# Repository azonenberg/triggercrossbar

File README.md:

# PROJECT STATUS

You probably don't want to build this as is, there's a couple of bugs. May or may not respin later on with fixes, for now I'm just bodging my prototype.

Bodge log at https://docs.google.com/document/d/14ighvhOLtBR-3ShkNhyRGlamA1f7WH5_sXfJCJYxb1o/edit

# What is it?

When finished, it will be a 1U rack-mountable appliance with a TBD number of BNC and/or SMA connectors on the back side for trigger inputs and outputs. Some will be input only, some output only, and some bidirectional. Exact mix is TBD.

Additionally, a front panel SMA input will be connected through a precision 10 GHz comparator (ADI HMC675LP3E) to an FPGA transceiver input, allowing single ended CDR triggering.

There may or may not be front panel SMA inputs/outputs connected to otherwise unused transceiver channels for expansion or additional trigger capabilities.

An Ethernet SCPI interface will allow configuration of an FPGA-based crossbar, with the internal CDR trigger as well as all of the input channels available as inputs. Any input can be forwarded to any output, allowing arbitrary cross-triggering of attached instruments without the need to recable.

Front panel LEDs with pulse stretching will display the states of trigger in/out ports.

This system is intended in part as a testbed to de-risk several future projects (validating stackup and power supply design etc), and to use up an FPGA that I had lying around the lab. Only one unit is ever expected to be built, so a functionally equivalent platform could definitely be built for lower cost.

# Physical architecture

# Trigger ports

Koaxis AL62-CC086F-RL10-6.00-MK (6" CC086F hand formable FEP jacket SMA - SMPM), length open to change based on final mechanical and board design.

## Input range

The range of the inputs should be sufficient to accommodate all common T&M instruments, which will likely require variable thresholding.

Representative instrument trigger output specs:

* PicoScope 6000E (bidirectional): not specified, need to measure
* PicoVNA 108: 3.3V into high-Z
* Siglent SSG5000X (bidirectional): 5V TTL for trigger, 3.3V CMOS for pulse
* Siglent SDG7000A: 5V TTL (voh = 3.8V)
* Teledyne LeCroy (all recent models): 1V into 1M ohm / 500 mV into 50 ohm by default, adjustable a bit?

## Output range

The range of the outputs should be compatible with all common T&M instruments, which will likely require variable swing.

Representative instrument trigger input specs:

* PicoScope 6000E (bidirectional): 2.5V CMOS high-z input, fixed 1.25V threshold
* PicoVNA 108: 3.3V CMOS high-Z, nominal 1.5V threshold
* Siglent SSG5000X (bidirectional): 5V TTL for trigger, 3.3V CMOS for pulse
* Siglent SDG7000A: 5V TTL (Vih = 2 to 5.5V)
* Teledyne LeCroy (all recent models): adjustable threshold up to +/- 400 mV or +/- 4V in 1x / 10x mode respectively

# Input buffer design

We need a total of seven inputs today, plan for at least ten to provide some margin

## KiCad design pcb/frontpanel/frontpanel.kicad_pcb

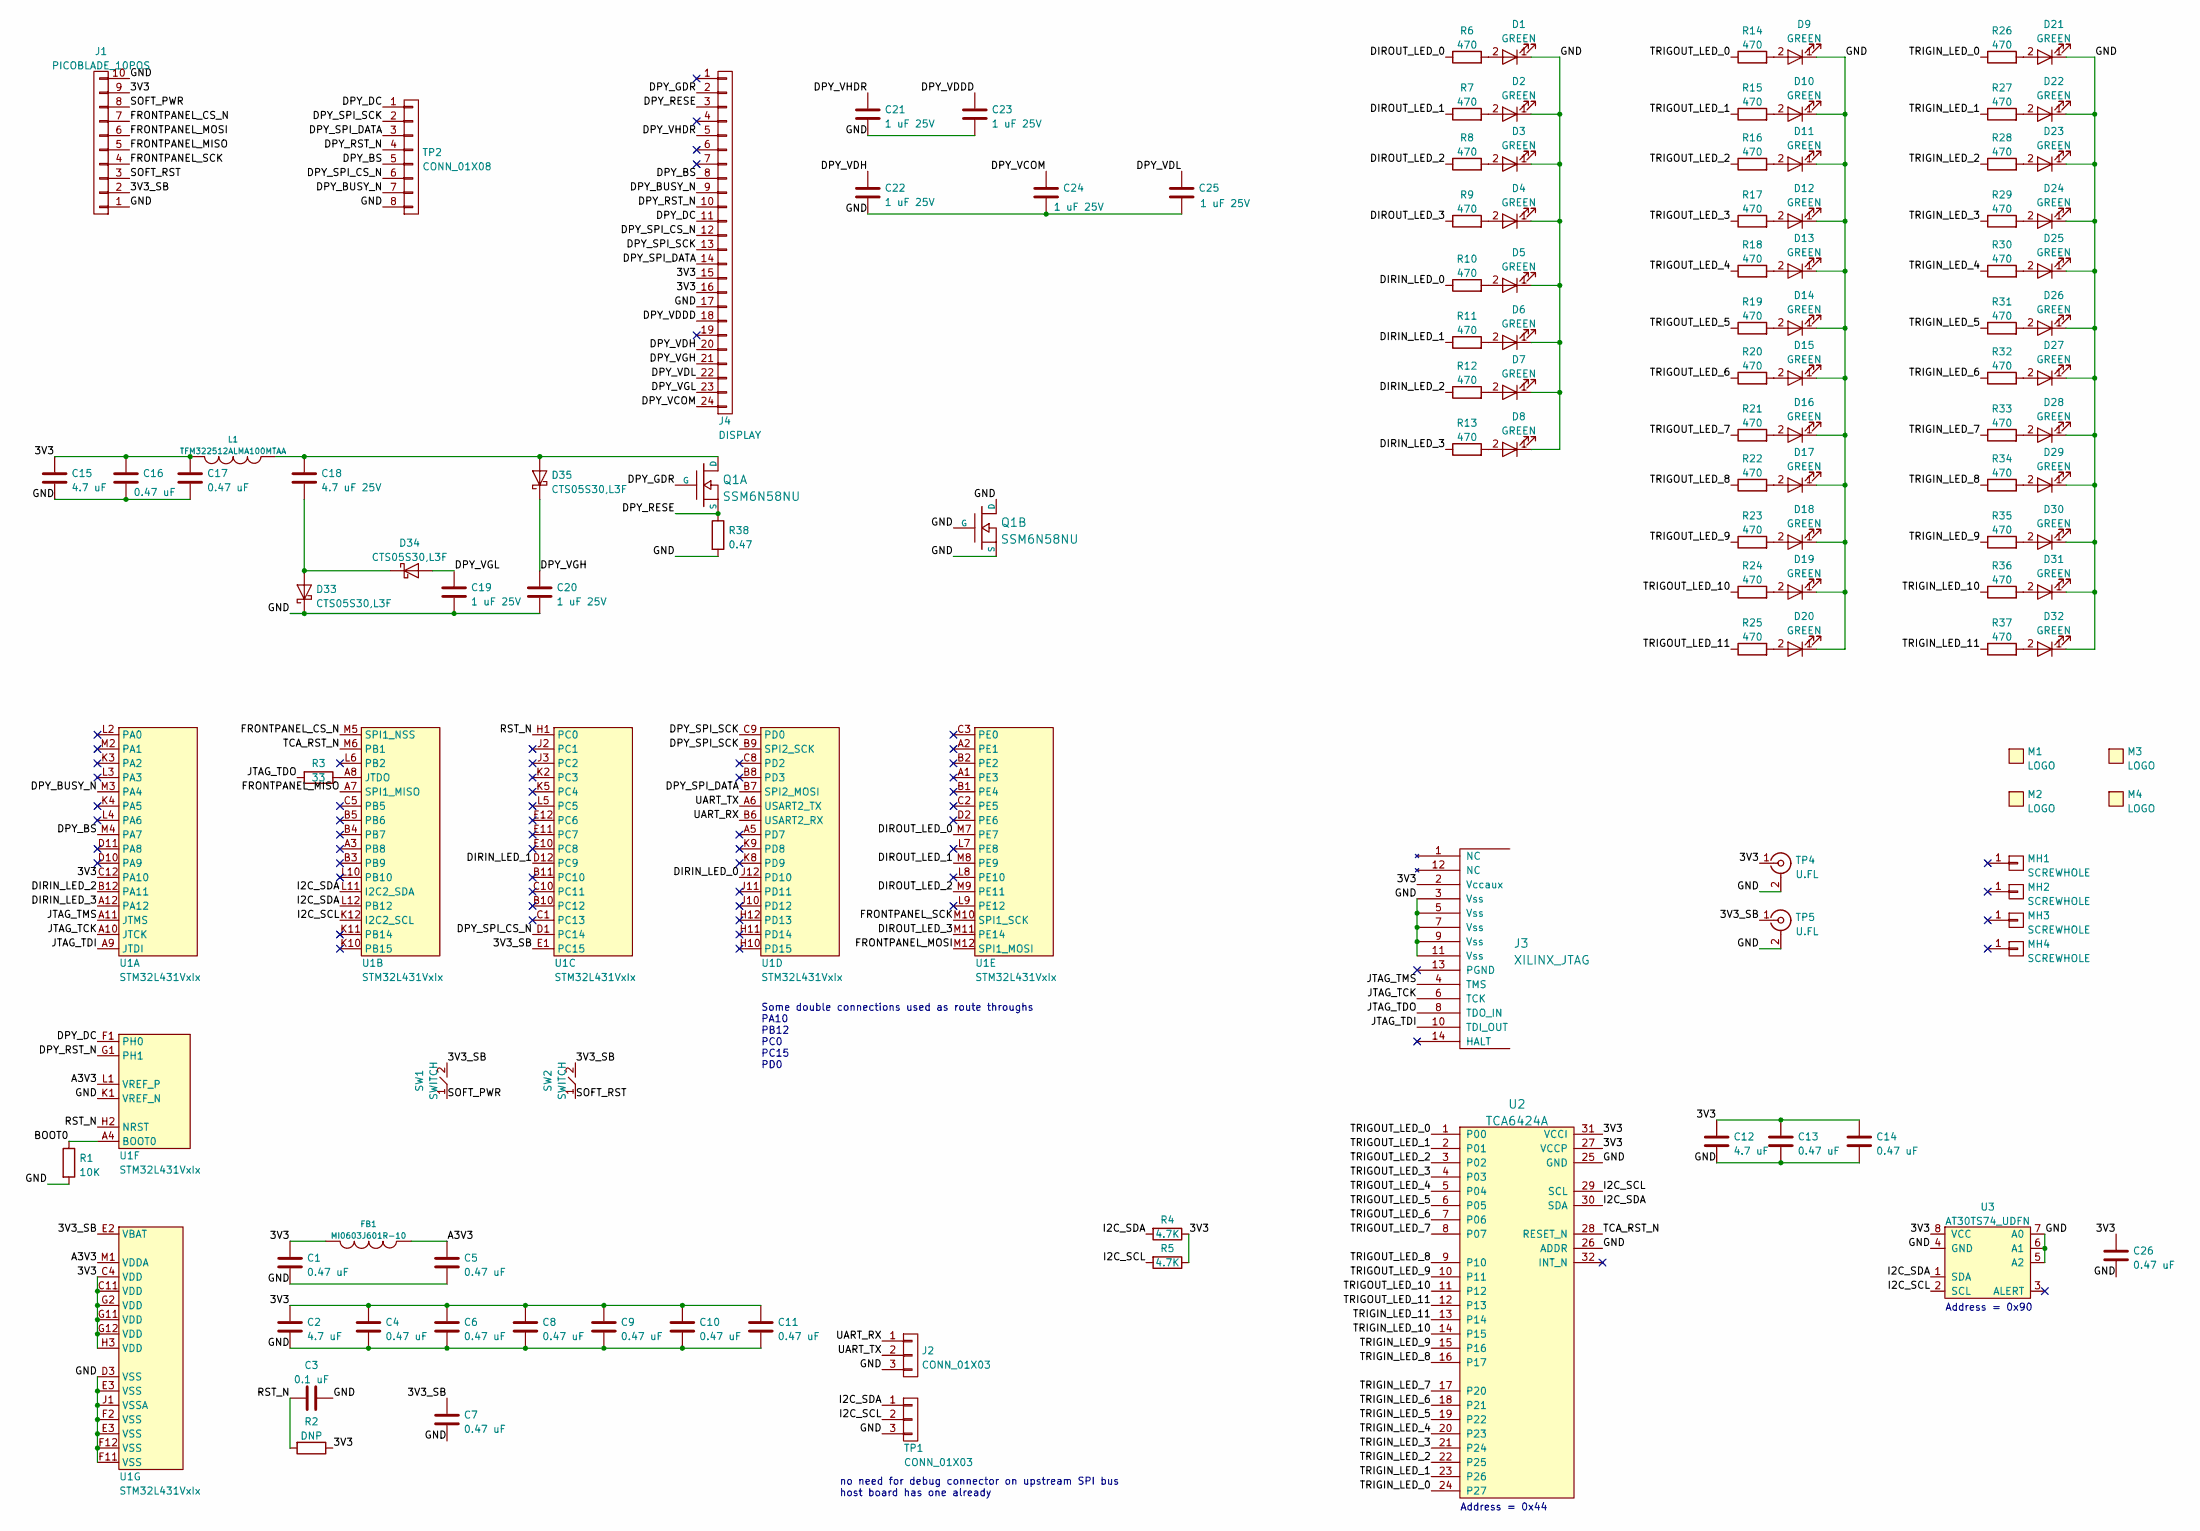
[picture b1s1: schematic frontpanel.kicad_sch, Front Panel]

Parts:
C1, C4, C5, C6, C7, C8, C9, C10, C11, C13, C14, C16, C17, C26: 0.47 uF; EIA_0402_CAP_NOSILK
C2, C12, C15: 4.7 uF; EIA_0603_CAP_NOSILK
C3: 0.1 uF; EIA_0402_CAP_NOSILK
C18: 4.7 uF 25V; EIA_0805_CAP_NOSILK
C19, C20, C21, C22, C23, C24, C25: 1 uF 25V; EIA_0805_CAP_NOSILK
D1, D2, D3, D4, D5, D6, D7, D8, D9, D10, D11, D12, D13, D14, D15, D16, D17, D18, D19, D20, D21, D22, D23, D24, D25, D26, D27, D28, D29, D30, D31, D32: GREEN; EIA_0603_LED
D33, D34, D35: CTS05S30,L3F; SOD882
FB1: MI0603J601R-10; EIA_0603_INDUCTOR_NOSILK
J1: PICOBLADE_10POS; CONN_MOLEX_PICOBLADE_10POS_0532611071
J2: CONN_01X03; CONN_HEADER_2.54MM_1x3
J3: XILINX_JTAG; XILINX_JTAG_PTH_MOLEX_0878311420
J4: DISPLAY; CONN_FFC_0.5MM_1x24_HIROSE_FH34SRJ-24S-0.5SH(50)
L1: TFM322512ALMA100MTAA; EIA_1210_CAP_NOSILK
M1: LOGO; LONGTHING-1200DPI
M2: LOGO; Logo_silk_WEEE_3.4x5mm
M3: LOGO; Logo_silk_OSHW_6x6mm
M4: LOGO; Logo_silk_ROHS_10x5.6mm
MH1, MH2, MH3, MH4: SCREWHOLE; MECHANICAL_CLEARANCEHOLE_4_40
Q1: SSM6N58NU; DFN_6_0.65MM_2x2MM_GDS
R1: 10K; EIA_0402_RES_NOSILK
R2: DNP; EIA_0402_RES_NOSILK
R3: 33; EIA_0402_RES_NOSILK
R4, R5: 4.7K; EIA_0402_RES_NOSILK
R6, R7, R8, R9, R10, R11, R12, R13, R14, R15, R16, R17, R18, R19, R20, R21, R22, R23, R24, R25, R26, R27, R28, R29, R30, R31, R32, R33, R34, R35, R36, R37: 470; EIA_0402_RES_NOSILK
R38: 0.47; EIA_0402_RES_NOSILK
SW1, SW2: SWITCH; SWITCH_RAFI_MICON_5
TP1: CONN_01X03; CONN_HEADER_2.54MM_1x3
TP2: CONN_01X08; CONN_HEADER_2.54MM_1x8
TP4, TP5: U.FL; CONN_U.FL_TE_1909763-1
U1: STM32L431VxIx; BGA_100_7x7_DEPOP_0.5MM_STM32_UFBGA100_OSHPARK
U2: TCA6424A; QFN_32_0.5MM_5x5MM
U3: AT30TS74_UDFN; DFN_8_0.5MM_2x3MM_TALL

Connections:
/3V3: C1.1, C2.1, C4.1, C6.1, C8.1, C9.1, C10.1, C11.1, C12.1, C13.1, C14.1, C15.1, C16.1, C17.1, C26.1, FB1.2, J1.9, J3.2 (Vccaux), J4.15, J4.16, L1.2, R2.1, R4.1, R5.1, TP4.1 (In), U1.C4 (VDD), U1.C11 (VDD), U1.C12 (PA10), U1.G2 (VDD), U1.G11 (VDD), U1.G12 (VDD), U1.H3 (VDD), U2.27 (VCCP), U2.31 (VCCI), U3.8 (VCC)
/3V3_SB: C7.1, J1.2, SW1.2, SW2.2, TP5.1 (In), U1.E1 (PC15), U1.E2 (VBAT)
/A3V3: C5.1, FB1.1, U1.L1 (VREF_P), U1.M1 (VDDA)
/BOOT0: R1.1, U1.A4 (BOOT0)
/DIRIN_LED_0: R10.1, U1.J12 (PD10)
/DIRIN_LED_1: R11.1, U1.D12 (PC9)
/DIRIN_LED_2: R12.1, U1.B12 (PA11)
/DIRIN_LED_3: R13.1, U1.A12
/DIROUT_LED_0: R6.1, U1.M7 (PE7)
/DIROUT_LED_1: R7.1, U1.M8 (PE9)
/DIROUT_LED_2: R8.1, U1.M9 (PE11)
/DIROUT_LED_3: R9.1, U1.M11 (PE14)
/DPY_BS: J4.8, TP2.5, U1.M4 (PA7)
/DPY_BUSY_N: J4.9, TP2.7, U1.M3 (PA4)
/DPY_DC: J4.11, TP2.1, U1.F1 (PH0)
/DPY_GDR: J4.2, Q1.G1 (G)
/DPY_RESE: J4.3, Q1.S1 (S), R38.1
/DPY_RST_N: J4.10, TP2.4, U1.G1 (PH1)
/DPY_SPI_CS_N: J4.12, TP2.6, U1.D1 (PC14)
/DPY_SPI_DATA: J4.14, TP2.3, U1.B7 (SPI2_MOSI)
/DPY_SPI_SCK: J4.13, TP2.2, U1.B9 (SPI2_SCK), U1.C9 (PD0)
/DPY_VCOM: C24.1, J4.24
/DPY_VDDD: C23.1, J4.18
/DPY_VDH: C22.1, J4.20
/DPY_VDL: C25.1, J4.22
/DPY_VGH: C20.1, D35.1 (K), J4.21
/DPY_VGL: C19.1, D34.2 (A), J4.23
/DPY_VHDR: C21.1, J4.5
/FRONTPANEL_CS_N: J1.7, U1.M5 (SPI1_NSS)
/FRONTPANEL_MISO: J1.5, U1.A7 (SPI1_MISO)
/FRONTPANEL_MOSI: J1.6, U1.M12 (SPI1_MOSI)
/FRONTPANEL_SCK: J1.4, U1.M10 (SPI1_SCK)
/GND: C1.2, C2.2, C3.2, C4.2, C5.2, C6.2, C7.2, C8.2, C9.2, C10.2, C11.2, C12.2, C13.2, C14.2, C15.2, C16.2, C17.2, C19.2, C20.2, C21.2, C22.2, C23.2, C24.2, C25.2, C26.2, D1.1 (K), D2.1 (K), D3.1 (K), D4.1 (K), D5.1 (K), D6.1 (K), D7.1 (K), D8.1 (K), D9.1 (K), D10.1 (K), D11.1 (K), D12.1 (K), D13.1 (K), D14.1 (K), D15.1 (K), D16.1 (K), D17.1 (K), D18.1 (K), D19.1 (K), D20.1 (K), D21.1 (K), D22.1 (K), D23.1 (K), D24.1 (K), D25.1 (K), D26.1 (K), D27.1 (K), D28.1 (K), D29.1 (K), D30.1 (K), D31.1 (K), D32.1 (K), D33.1 (K), J1.1, J1.10, J2.3, J3.3 (Vss), J3.5 (Vss), J3.7 (Vss), J3.9 (Vss), J3.11 (Vss), J4.17, Q1.D2 (D), Q1.G2 (G), Q1.S2 (S), R1.2, R38.2, TP1.3, TP2.8, TP4.2 (Ext), TP5.2 (Ext), U1.D3 (VSS), U1.E3 (VSS), U1.F2 (VSS), U1.F11 (VSS), U1.F12 (VSS), U1.J1 (VSSA), U1.K1 (VREF_N), U2.25 (GND), U2.26 (ADDR), U3.4 (GND), U3.5 (A2), U3.6 (A1), U3.7 (A0)
/I2C_SCL: R5.2, TP1.2, U1.K12 (I2C2_SCL), U2.29 (SCL), U3.2 (SCL)
/I2C_SDA: R4.2, TP1.1, U1.L11 (I2C2_SDA), U1.L12 (PB12), U2.30 (SDA), U3.1 (SDA)
/JTAG_TCK: J3.6 (TCK), U1.A10 (JTCK)
/JTAG_TDI: J3.10 (TDI_OUT), U1.A9 (JTDI)
/JTAG_TDO: J3.8 (TDO_IN), R3.2
/JTAG_TMS: J3.4 (TMS), U1.A11 (JTMS)
/RST_N: C3.1, R2.2, U1.H1 (PC0), U1.H2 (NRST)
/SOFT_PWR: J1.8, SW1.1
/SOFT_RST: J1.3, SW2.1
/TCA_RST_N: U1.M6 (PB1), U2.28 (RESET_N)
/TRIGIN_LED_0: R26.1, U2.24 (P27)
/TRIGIN_LED_1: R27.1, U2.23 (P26)
/TRIGIN_LED_2: R28.1, U2.22 (P25)
/TRIGIN_LED_3: R29.1, U2.21 (P24)
/TRIGIN_LED_4: R30.1, U2.20 (P23)
/TRIGIN_LED_5: R31.1, U2.19 (P22)
/TRIGIN_LED_6: R32.1, U2.18 (P21)
/TRIGIN_LED_7: R33.1, U2.17 (P20)
/TRIGIN_LED_8: R34.1, U2.16 (P17)
/TRIGIN_LED_9: R35.1, U2.15 (P16)
/TRIGIN_LED_10: R36.1, U2.14 (P15)
/TRIGIN_LED_11: R37.1, U2.13 (P14)
/TRIGOUT_LED_0: R14.1, U2.1 (P00)
/TRIGOUT_LED_1: R15.1, U2.2 (P01)
/TRIGOUT_LED_2: R16.1, U2.3 (P02)
/TRIGOUT_LED_3: R17.1, U2.4 (P03)
/TRIGOUT_LED_4: R18.1, U2.5 (P04)
/TRIGOUT_LED_5: R19.1, U2.6 (P05)
/TRIGOUT_LED_6: R20.1, U2.7 (P06)
/TRIGOUT_LED_7: R21.1, U2.8 (P07)
/TRIGOUT_LED_8: R22.1, U2.9 (P10)
/TRIGOUT_LED_9: R23.1, U2.10 (P11)
/TRIGOUT_LED_10: R24.1, U2.11 (P12)
/TRIGOUT_LED_11: R25.1, U2.12 (P13)
/UART_RX: J2.1, U1.B6 (USART2_RX)
/UART_TX: J2.2, U1.A6 (USART2_TX)
unnamed: C18.1, D35.2 (A), L1.1, Q1.D1 (D)
unnamed: C18.2, D33.2 (A), D34.1 (K)
unnamed: D1.2 (A), R6.2
unnamed: D2.2 (A), R7.2
unnamed: D3.2 (A), R8.2
unnamed: D4.2 (A), R9.2
unnamed: D5.2 (A), R10.2
unnamed: D6.2 (A), R11.2
unnamed: D7.2 (A), R12.2
unnamed: D8.2 (A), R13.2
unnamed: D9.2 (A), R14.2
unnamed: D10.2 (A), R15.2
unnamed: D11.2 (A), R16.2
unnamed: D12.2 (A), R17.2
unnamed: D13.2 (A), R18.2
unnamed: D14.2 (A), R19.2
unnamed: D15.2 (A), R20.2
unnamed: D16.2 (A), R21.2
unnamed: D17.2 (A), R22.2
unnamed: D18.2 (A), R23.2
unnamed: D19.2 (A), R24.2
unnamed: D20.2 (A), R25.2
unnamed: D21.2 (A), R26.2
unnamed: D22.2 (A), R27.2
unnamed: D23.2 (A), R28.2
unnamed: D24.2 (A), R29.2
unnamed: D25.2 (A), R30.2
unnamed: D26.2 (A), R31.2
unnamed: D27.2 (A), R32.2
unnamed: D28.2 (A), R33.2
unnamed: D29.2 (A), R34.2
unnamed: D30.2 (A), R35.2
unnamed: D31.2 (A), R36.2
unnamed: D32.2 (A), R37.2
unnamed: R3.1, U1.A8 (JTDO)

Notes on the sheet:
Address = 0x90
no need for debug connector on upstream SPI bus host board has one already
Address = 0x44
Some double connections used as route throughs PA10 PB12 PC0 PC15 PD0

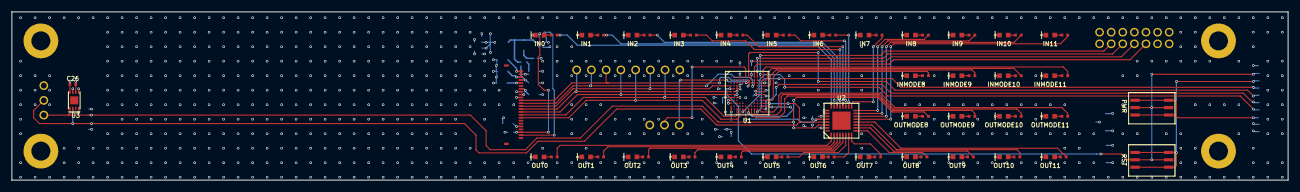
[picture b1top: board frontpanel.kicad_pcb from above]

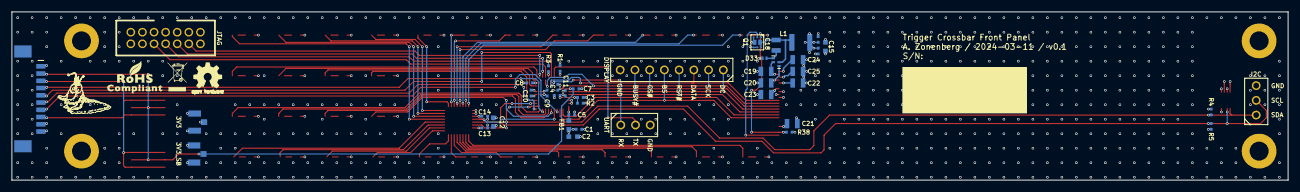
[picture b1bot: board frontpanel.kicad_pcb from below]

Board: 4 copper layers, 220.0 x 29.0 mm, 123 parts (52 on the bottom side), 104 nets.

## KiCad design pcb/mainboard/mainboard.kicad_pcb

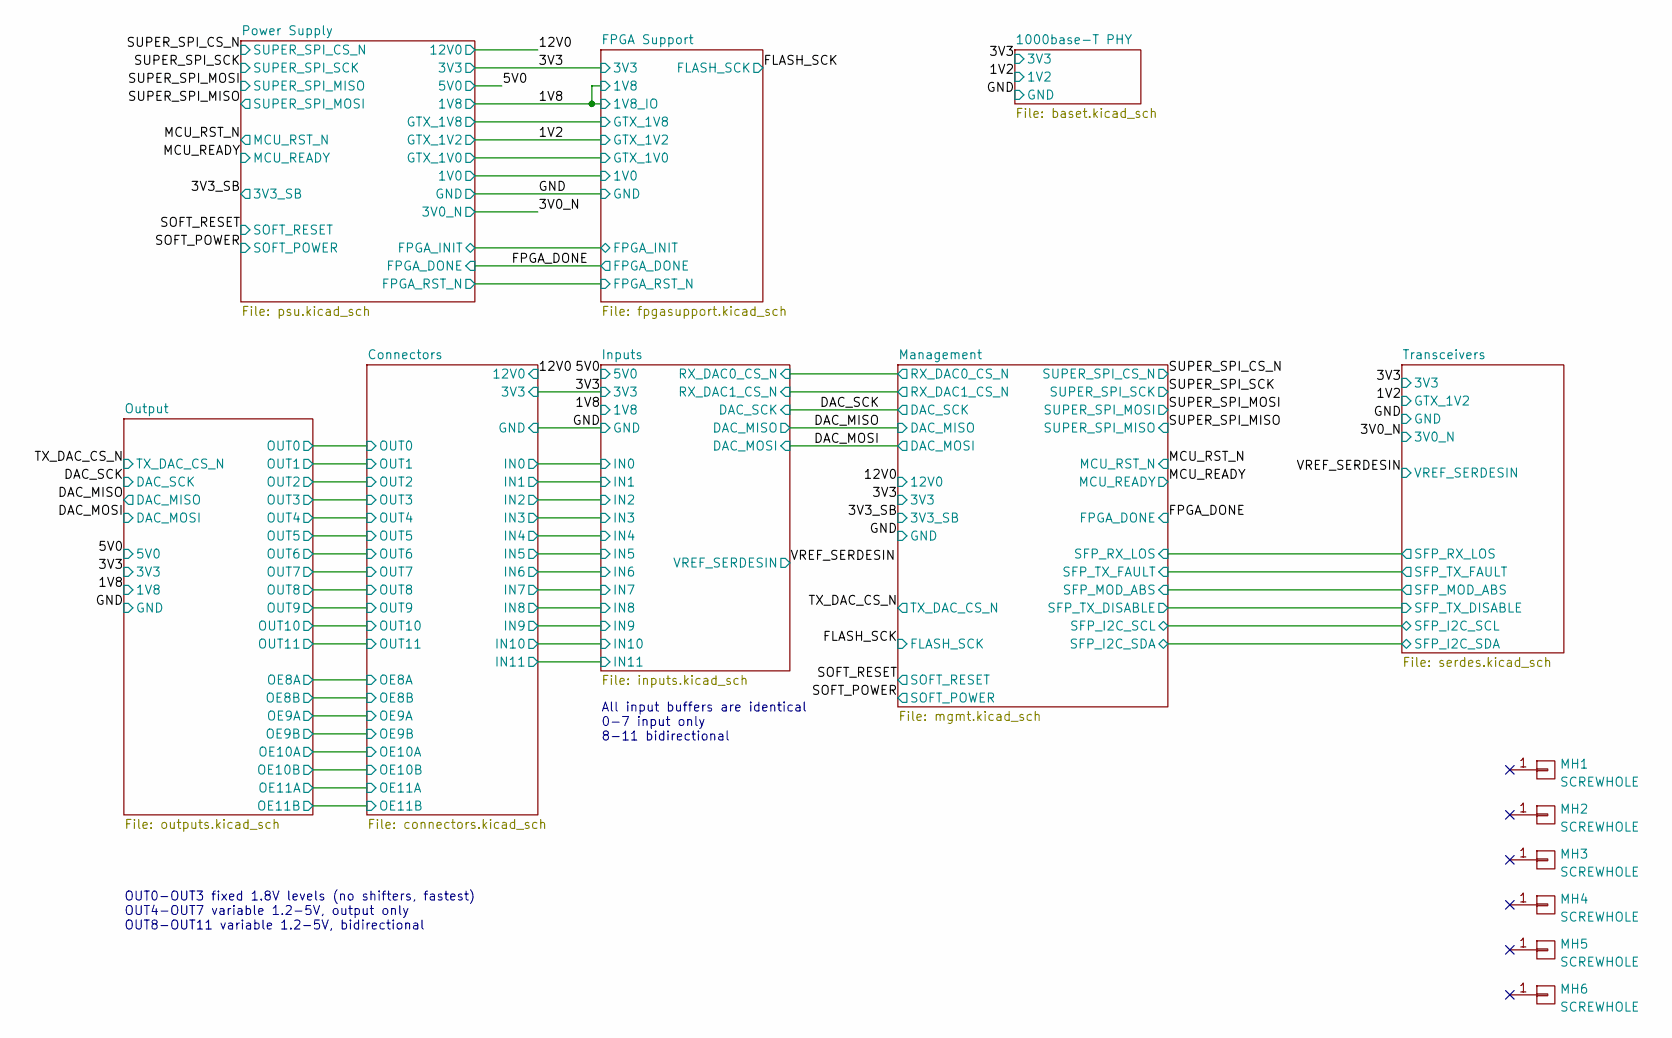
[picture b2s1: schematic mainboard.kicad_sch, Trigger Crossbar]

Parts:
MH1, MH2, MH3, MH4, MH5, MH6: SCREWHOLE; MECHANICAL_CLEARANCEHOLE_4_40

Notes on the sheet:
All input buffers are identical 0-7 input only 8-11 bidirectional
OUT0-OUT3 fixed 1.8V levels (no shifters, fastest) OUT4-OUT7 variable 1.2-5V, output only OUT8-OUT11 variable 1.2-5V, bidirectional

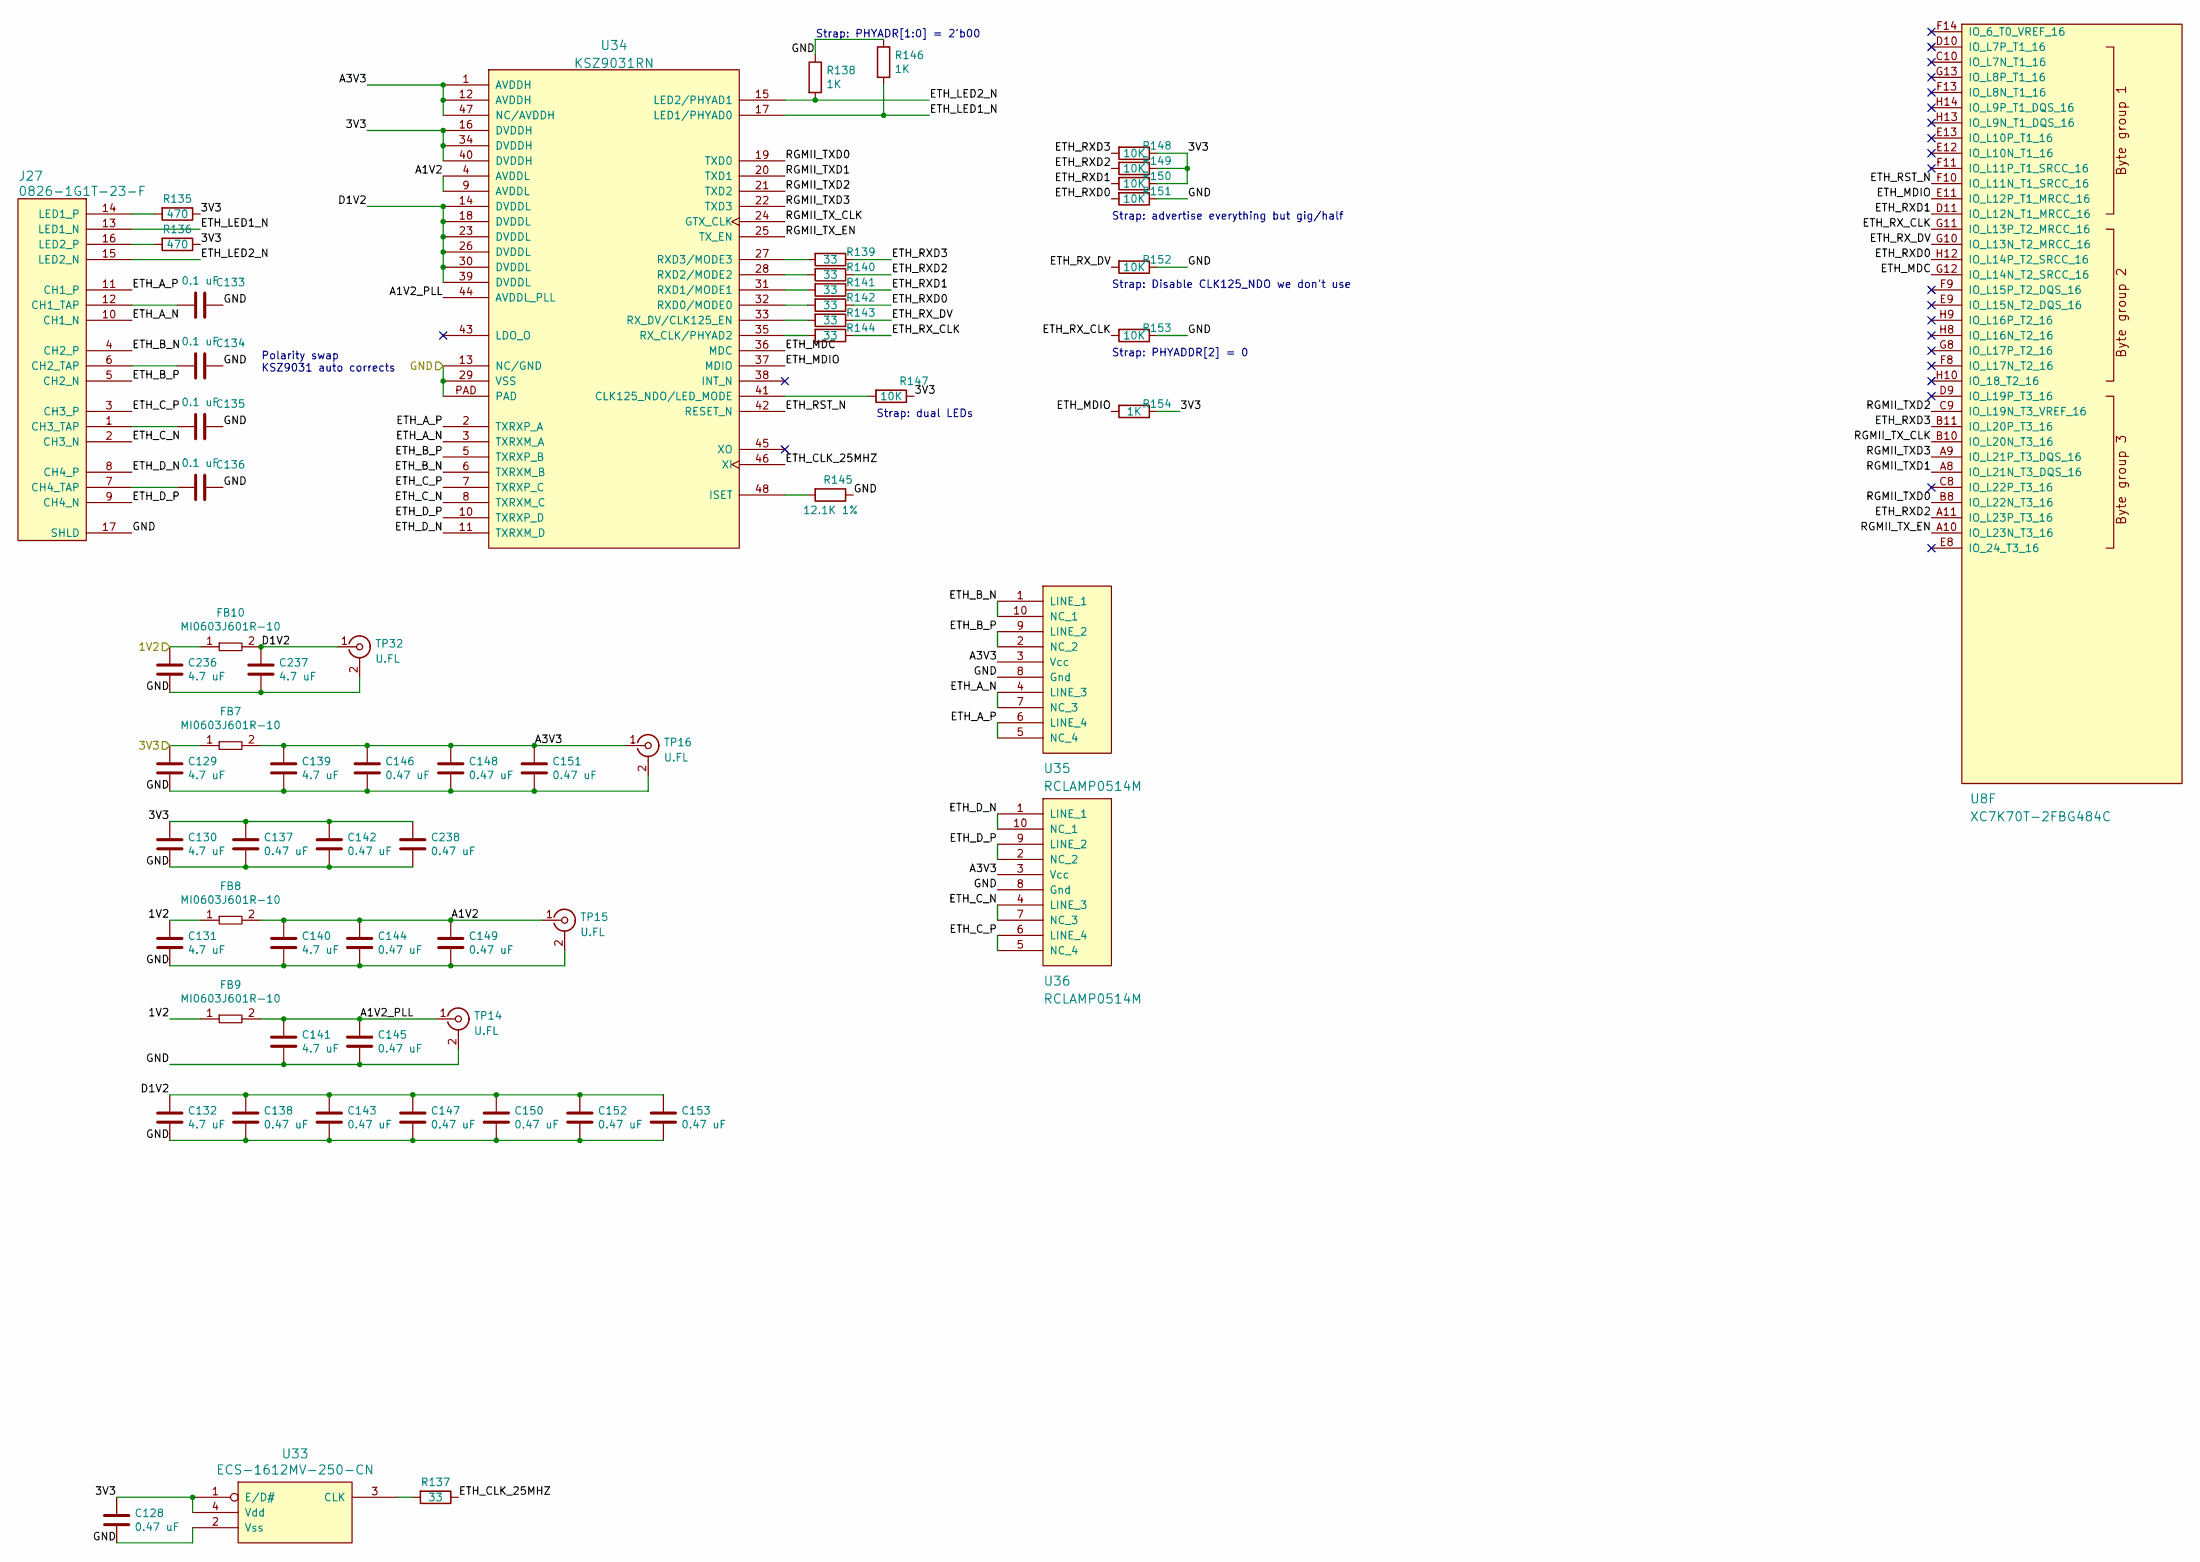
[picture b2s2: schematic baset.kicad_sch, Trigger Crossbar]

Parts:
C128, C137, C138, C142, C143, C144, C145, C146, C147, C148, C149, C150, C151, C152, C153, C238: 0.47 uF; EIA_0402_CAP_NOSILK
C129, C130, C131, C132, C139, C140, C141, C236, C237: 4.7 uF; EIA_0603_CAP_NOSILK
C133, C134, C135, C136: 0.1 uF; EIA_0402_CAP_NOSILK
FB7, FB8, FB9, FB10: MI0603J601R-10; EIA_0603_INDUCTOR_NOSILK
J27: 0826-1G1T-23-F; CONN_BELFUSE_0826_1G1T_23_F
R135, R136: 470; EIA_0402_RES_NOSILK
R137, R139, R140, R141, R142, R143, R144: 33; EIA_0402_RES_NOSILK
R138, R146, R154: 1K; EIA_0402_RES_NOSILK
R145: 12.1K 1%; EIA_0402_RES_NOSILK
R147, R148, R149, R150, R151, R152, R153: 10K; EIA_0402_RES_NOSILK
TP14, TP15, TP16, TP32: U.FL; CONN_U.FL_TE_1909763-1
U8: XC7K70T-2FBG484C; BGA_484_22x22_FULLARRAY_1MM
U33: ECS-1612MV-250-CN; OSCILLATOR_1.6x1.2
U34: KSZ9031RN; QFN_48_0.5MM_7x7MM
U35, U36: RCLAMP0514M; SOP_10_0.5MM_3MM

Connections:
/1V2: C131.1, C236.1, FB8.1, FB9.1, FB10.1; also elsewhere on the board
/3V3: C128.1, C129.1, C130.1, C137.1, C142.1, C238.1, FB7.1, R135.1, R136.1, R147.1, R148.1, R149.1, R150.1, R154.1, U33.1 (E/D#), U33.4 (Vdd), U34.16 (DVDDH), U34.34 (DVDDH), U34.40 (DVDDH); also elsewhere on the board
/1000base-T PHY/A1V2: C140.1, C144.1, C149.1, FB8.2, TP15.1 (In), U34.4 (AVDDL), U34.9 (AVDDL)
/1000base-T PHY/A1V2_PLL: C141.1, C145.1, FB9.2, TP14.1 (In), U34.44 (AVDDL_PLL)
/1000base-T PHY/A3V3: C139.1, C146.1, C148.1, C151.1, FB7.2, TP16.1 (In), U34.1 (AVDDH), U34.12 (AVDDH), U34.47 (NC/AVDDH), U35.3 (Vcc), U36.3 (Vcc)
/1000base-T PHY/D1V2: C132.1, C138.1, C143.1, C147.1, C150.1, C152.1, C153.1, C237.1, FB10.2, TP32.1 (In), U34.14 (DVDDL), U34.18 (DVDDL), U34.23 (DVDDL), U34.26 (DVDDL), U34.30 (DVDDL), U34.39 (DVDDL)
/1000base-T PHY/ETH_A_N: J27.10 (CH1_N), U34.3 (TXRXM_A), U35.4 (LINE_3), U35.7 (NC_3)
/1000base-T PHY/ETH_A_P: J27.11 (CH1_P), U34.2 (TXRXP_A), U35.5 (NC_4), U35.6 (LINE_4)
/1000base-T PHY/ETH_B_N: J27.4 (CH2_P), U34.6 (TXRXM_B), U35.1 (LINE_1), U35.10 (NC_1)
/1000base-T PHY/ETH_B_P: J27.5 (CH2_N), U34.5 (TXRXP_B), U35.2 (NC_2), U35.9 (LINE_2)
/1000base-T PHY/ETH_CLK_25MHZ: R137.1, U34.46 (XI)
/1000base-T PHY/ETH_C_N: J27.2 (CH3_N), U34.8 (TXRXM_C), U36.4 (LINE_3), U36.7 (NC_3)
/1000base-T PHY/ETH_C_P: J27.3 (CH3_P), U34.7 (TXRXP_C), U36.5 (NC_4), U36.6 (LINE_4)
/1000base-T PHY/ETH_D_N: J27.8 (CH4_P), U34.11 (TXRXM_D), U36.1 (LINE_1), U36.10 (NC_1)
/1000base-T PHY/ETH_D_P: J27.9 (CH4_N), U34.10 (TXRXP_D), U36.2 (NC_2), U36.9 (LINE_2)
/1000base-T PHY/ETH_LED1_N: J27.13 (LED1_N), R146.2, U34.17 (LED1/PHYAD0)
/1000base-T PHY/ETH_LED2_N: J27.15 (LED2_N), R138.2, U34.15 (LED2/PHYAD1)
/1000base-T PHY/ETH_MDC: U8.G12 (IO_L14N_T2_SRCC_16), U34.36 (MDC)
/1000base-T PHY/ETH_MDIO: R154.2, U8.E11 (IO_L12P_T1_MRCC_16), U34.37 (MDIO)
/1000base-T PHY/ETH_RST_N: U8.F10 (IO_L11N_T1_SRCC_16), U34.42 (RESET_N)
/1000base-T PHY/ETH_RXD0: R142.1, R151.2, U8.H12 (IO_L14P_T2_SRCC_16)
/1000base-T PHY/ETH_RXD1: R141.1, R150.2, U8.D11 (IO_L12N_T1_MRCC_16)
/1000base-T PHY/ETH_RXD2: R140.1, R149.2, U8.A11 (IO_L23P_T3_16)
/1000base-T PHY/ETH_RXD3: R139.1, R148.2, U8.B11 (IO_L20P_T3_16)
/1000base-T PHY/ETH_RX_CLK: R144.1, R153.2, U8.G11 (IO_L13P_T2_MRCC_16)
/1000base-T PHY/ETH_RX_DV: R143.1, R152.2, U8.G10 (IO_L13N_T2_MRCC_16)
/1000base-T PHY/RGMII_TXD0: U8.B8 (IO_L22N_T3_16), U34.19 (TXD0)
/1000base-T PHY/RGMII_TXD1: U8.A8 (IO_L21N_T3_DQS_16), U34.20 (TXD1)
/1000base-T PHY/RGMII_TXD2: U8.C9 (IO_L19N_T3_VREF_16), U34.21 (TXD2)
/1000base-T PHY/RGMII_TXD3: U8.A9 (IO_L21P_T3_DQS_16), U34.22 (TXD3)
/1000base-T PHY/RGMII_TX_CLK: U8.B10 (IO_L20N_T3_16), U34.24 (GTX_CLK)
/1000base-T PHY/RGMII_TX_EN: U8.A10 (IO_L23N_T3_16), U34.25 (TX_EN)
/GND: C128.2, C129.2, C130.2, C131.2, C132.2, C133.1, C134.1, C135.1, C136.1, C137.2, C138.2, C139.2, C140.2, C141.2, C142.2, C143.2, C144.2, C145.2, C146.2, C147.2, C148.2, C149.2, C150.2, C151.2, C152.2, C153.2, C236.2, C237.2, C238.2, J27.17 (SHLD), R138.1, R145.1, R146.1, R151.1, R152.1, R153.1, TP14.2 (Ext), TP15.2 (Ext), TP16.2 (Ext), TP32.2 (Ext), U33.2 (Vss), U34.13 (NC/GND), U34.29 (VSS), U34.PAD, U35.8 (Gnd), U36.8 (Gnd); also elsewhere on the board
unnamed: C133.2, J27.12 (CH1_TAP)
unnamed: C134.2, J27.6 (CH2_TAP)
unnamed: C135.2, J27.1 (CH3_TAP)
unnamed: C136.2, J27.7 (CH4_TAP)
unnamed: J27.14 (LED1_P), R135.2
unnamed: J27.16 (LED2_P), R136.2
unnamed: R137.2, U33.3 (CLK)
unnamed: R139.2, U34.27 (RXD3/MODE3)
unnamed: R140.2, U34.28 (RXD2/MODE2)
unnamed: R141.2, U34.31 (RXD1/MODE1)
unnamed: R142.2, U34.32 (RXD0/MODE0)
unnamed: R143.2, U34.33 (RX_DV/CLK125_EN)
unnamed: R144.2, U34.35 (RX_CLK/PHYAD2)
unnamed: R145.2, U34.48 (ISET)
unnamed: R147.2, U34.41 (CLK125_NDO/LED_MODE)

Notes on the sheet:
Polarity swap KSZ9031 auto corrects
Strap: PHYADR[1:0] = 2'b00
Strap: PHYADDR[2] = 0
Strap: advertise everything but gig/half
Strap: dual LEDs
Strap: Disable CLK125_NDO we don't use

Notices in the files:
firmware/main/bsp/hwinit.cpp:
Copyright (c) 2023-2025 Andrew D. Zonenberg and contributors
All rights reserved.
firmware/super/oldmain/main.cpp:
Copyright (c) 2023-2024 Andrew D. Zonenberg and contributors
